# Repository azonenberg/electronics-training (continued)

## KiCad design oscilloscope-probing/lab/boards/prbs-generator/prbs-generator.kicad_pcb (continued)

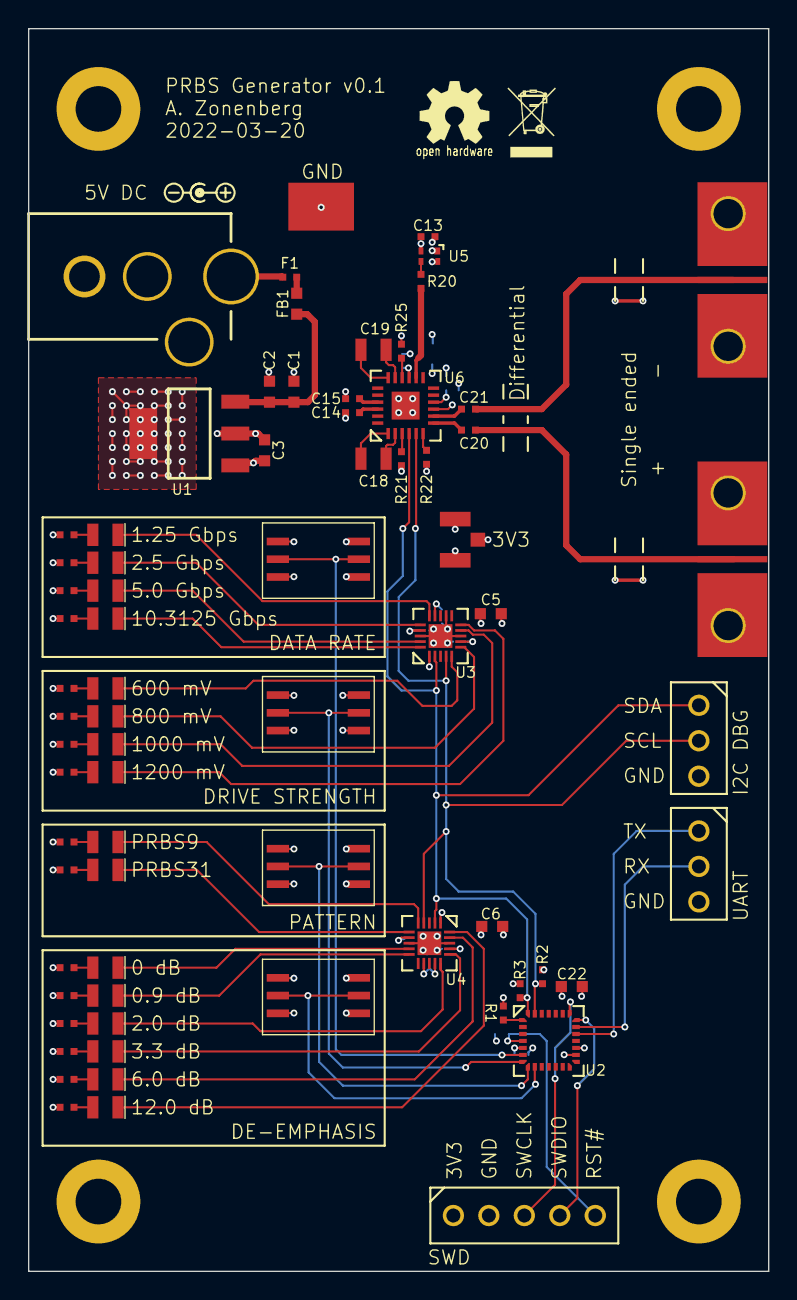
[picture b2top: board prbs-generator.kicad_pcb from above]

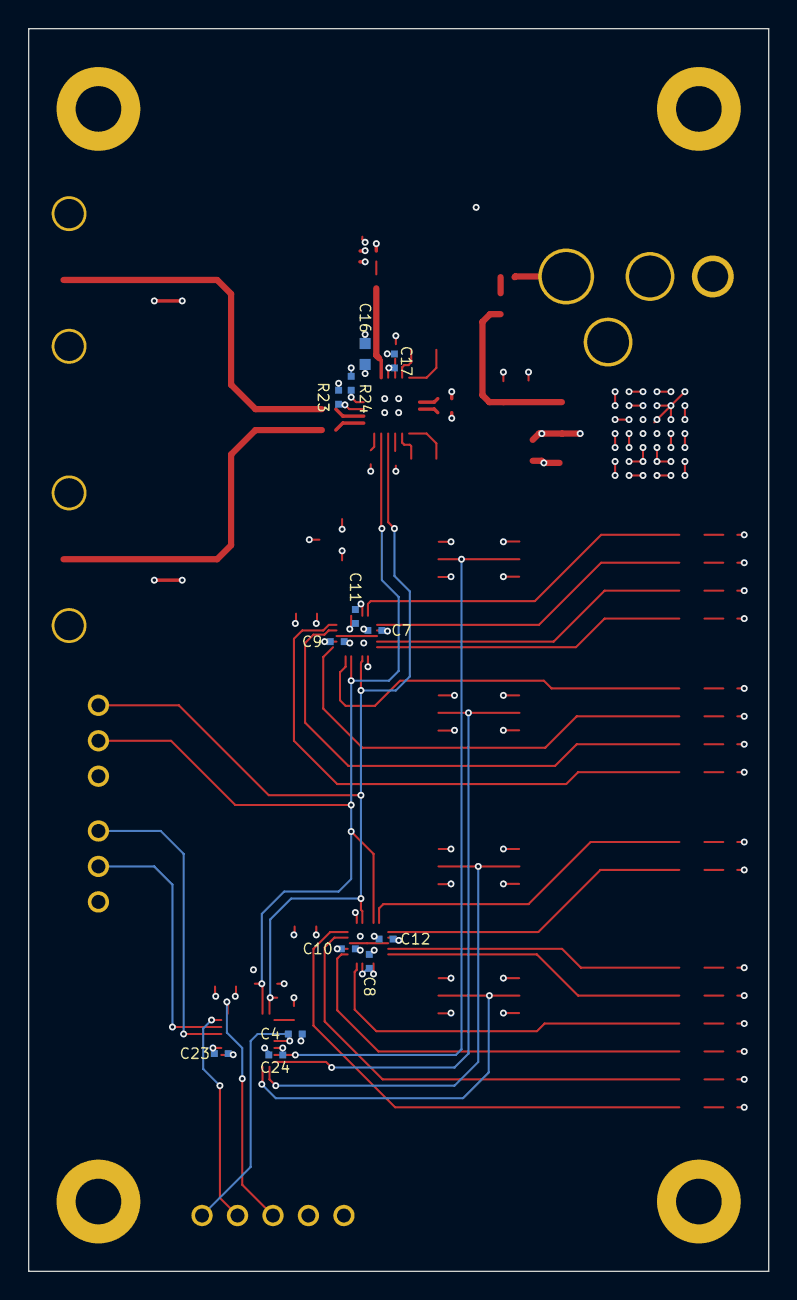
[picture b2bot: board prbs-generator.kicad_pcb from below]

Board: 4 copper layers, 53.0 x 89.0 mm, 92 parts (13 on the bottom side), 66 nets.

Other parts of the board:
G1: LOGO; Logo_silk_OSHW_6x6mm
G2: LOGO; Logo_silk_WEEE_3.4x5mm
G3: LOGO; Logo_silk_polarity_center_5x1.4mm

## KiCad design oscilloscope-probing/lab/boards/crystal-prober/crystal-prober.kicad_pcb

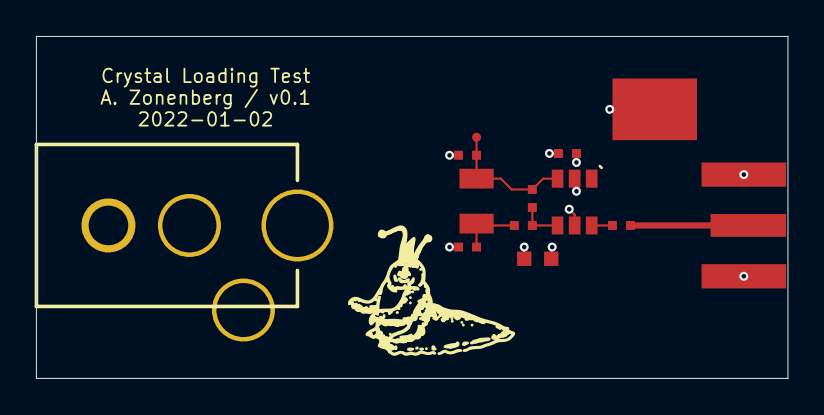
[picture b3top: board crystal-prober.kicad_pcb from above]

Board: 4 copper layers, 41.8 x 19.0 mm, 13 parts (0 on the bottom side), 7 nets.

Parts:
C1: 4.7 uF; EIA_0603_CAP_NOSILK
C2: 0.47 uF; EIA_0402_CAP_NOSILK
C3, C4: 8 pF; EIA_0402_CAP_NOSILK
J1: BARREL_JACK; CONN_CUI_PJ-058BH_HIPWR_BARREL_NOSLOT
J2: SMA-J-P-H-ST-EM1; CONN_SMA_EDGE_SAMTEC_SMA_J_P_H_ST_EM1
J3: TESTPOINT; TESTPOINT_SMT_0.5MM
J4: TESTCLIP; TESTPOINT_SMT_KEYSTONE_5016
R1: 1M; EIA_0402_RES_NOSILK
R2: 324K; EIA_0402_RES_NOSILK
R3: 33; EIA_0402_RES_NOSILK
U1: SN74LVC1GX04; SOT23_6
Y1: ABS07-32.768KHZ-4-T; CRYSTAL_3.2x1.5MM

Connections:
/3V3: C1.1, C2.1, J1.1, U1.5
/GND: C1.2, C2.2, C3.2, C4.2, J1.2, J2.2, J4.1, U1.2
/VOUT: R3.2, U1.6
/VOUT_TERM: J2.1, R3.1
/X1: C3.1, J3.1, R1.2, U1.3, Y1.1
/X2: R1.1, R2.1, U1.4
/X2X: C4.1, R2.2, Y1.2

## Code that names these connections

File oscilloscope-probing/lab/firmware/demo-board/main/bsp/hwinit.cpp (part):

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
void BSP_InitUART()
{
	//Initialize the UART for local console: 115.2 Kbps using PA9 for UART1 transmit and PA10 for UART1 receive
	//TODO: nice interface for enabling UART interrupts
	static GPIOPin uart_tx(&GPIOA, 9, GPIOPin::MODE_PERIPHERAL, GPIOPin::SLEW_SLOW, 7);
	static GPIOPin uart_rx(&GPIOA, 10, GPIOPin::MODE_PERIPHERAL, GPIOPin::SLEW_SLOW, 7);

	//Enable the UART interrupt
	NVIC_EnableIRQ(37);
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	//Wait a bit before initializing FMC in case something goes bad
	g_logTimer.Sleep(1000);

	static GPIOPin fmc_ad0(&GPIOD, 14, GPIOPin::MODE_PERIPHERAL, GPIOPin::SLEW_VERYFAST, 12);
	static GPIOPin fmc_ad1(&GPIOD, 15, GPIOPin::MODE_PERIPHERAL, GPIOPin::SLEW_VERYFAST, 12);
	static GPIOPin fmc_ad2(&GPIOD, 0, GPIOPin::MODE_PERIPHERAL, GPIOPin::SLEW_VERYFAST, 12);
	static GPIOPin fmc_ad3(&GPIOD, 1, GPIOPin::MODE_PERIPHERAL, GPIOPin::SLEW_VERYFAST, 12);
	static GPIOPin fmc_ad4(&GPIOE, 7, GPIOPin::MODE_PERIPHERAL, GPIOPin::SLEW_VERYFAST, 12);
	static GPIOPin fmc_ad5(&GPIOE, 8, GPIOPin::MODE_PERIPHERAL, GPIOPin::SLEW_VERYFAST, 12);
	static GPIOPin fmc_ad6(&GPIOE, 9, GPIOPin::MODE_PERIPHERAL, GPIOPin::SLEW_VERYFAST, 12);
	static GPIOPin fmc_ad7(&GPIOE, 10, GPIOPin::MODE_PERIPHERAL, GPIOPin::SLEW_VERYFAST, 12);
	static GPIOPin fmc_ad8(&GPIOE, 11, GPIOPin::MODE_PERIPHERAL, GPIOPin::SLEW_VERYFAST, 12);
	static GPIOPin fmc_ad9(&GPIOE, 12, GPIOPin::MODE_PERIPHERAL, GPIOPin::SLEW_VERYFAST, 12);
	static GPIOPin fmc_ad10(&GPIOE, 13, GPIOPin::MODE_PERIPHERAL, GPIOPin::SLEW_VERYFAST, 12);
	static GPIOPin fmc_ad11(&GPIOE, 14, GPIOPin::MODE_PERIPHERAL, GPIOPin::SLEW_VERYFAST, 12);
	static GPIOPin fmc_ad12(&GPIOE, 15, GPIOPin::MODE_PERIPHERAL, GPIOPin::SLEW_VERYFAST, 12);
	static GPIOPin fmc_ad13(&GPIOD, 8, GPIOPin::MODE_PERIPHERAL, GPIOPin::SLEW_VERYFAST, 12);
	static GPIOPin fmc_ad14(&GPIOD, 9, GPIOPin::MODE_PERIPHERAL, GPIOPin::SLEW_VERYFAST, 12);
	static GPIOPin fmc_ad15(&GPIOD, 10, GPIOPin::MODE_PERIPHERAL, GPIOPin::SLEW_VERYFAST, 12);

	static GPIOPin fmc_a16(&GPIOD, 11, GPIOPin::MODE_PERIPHERAL, GPIOPin::SLEW_VERYFAST, 12);
	static GPIOPin fmc_a17(&GPIOD, 12, GPIOPin::MODE_PERIPHERAL, GPIOPin::SLEW_VERYFAST, 12);
	static GPIOPin fmc_a18(&GPIOD, 13, GPIOPin::MODE_PERIPHERAL, GPIOPin::SLEW_VERYFAST, 12);
	static GPIOPin fmc_a19(&GPIOE, 3, GPIOPin::MODE_PERIPHERAL, GPIOPin::SLEW_VERYFAST, 12);
	static GPIOPin fmc_a20(&GPIOE, 4, GPIOPin::MODE_PERIPHERAL, GPIOPin::SLEW_VERYFAST, 12);
	static GPIOPin fmc_a21(&GPIOE, 5, GPIOPin::MODE_PERIPHERAL, GPIOPin::SLEW_VERYFAST, 12);
	static GPIOPin fmc_a22(&GPIOE, 6, GPIOPin::MODE_PERIPHERAL, GPIOPin::SLEW_VERYFAST, 12);
	//no A23...25 pinned out on this board

	static GPIOPin fmc_nl_nadv(&GPIOB, 7, GPIOPin::MODE_PERIPHERAL, GPIOPin::SLEW_VERYFAST, 12);
	static GPIOPin fmc_nwait(&GPIOD, 6, GPIOPin::MODE_PERIPHERAL, GPIOPin::SLEW_VERYFAST, 12);
	static GPIOPin fmc_ne1(&GPIOD, 7, GPIOPin::MODE_PERIPHERAL, GPIOPin::SLEW_VERYFAST, 12);
	static GPIOPin fmc_ne2(&GPIOC, 8, GPIOPin::MODE_PERIPHERAL, GPIOPin::SLEW_VERYFAST, 9);
	static GPIOPin fmc_ne3(&GPIOG, 6, GPIOPin::MODE_PERIPHERAL, GPIOPin::SLEW_VERYFAST, 12);
	static GPIOPin fmc_ne4(&GPIOG, 12, GPIOPin::MODE_PERIPHERAL, GPIOPin::SLEW_VERYFAST, 12);

	static GPIOPin fmc_clk(&GPIOD, 3, GPIOPin::MODE_PERIPHERAL, GPIOPin::SLEW_VERYFAST, 12);
	static GPIOPin fmc_noe(&GPIOD, 4, GPIOPin::MODE_PERIPHERAL, GPIOPin::SLEW_VERYFAST, 12);
	static GPIOPin fmc_nwe(&GPIOD, 5, GPIOPin::MODE_PERIPHERAL, GPIOPin::SLEW_VERYFAST, 12);
	static GPIOPin fmc_nbl0(&GPIOE, 0, GPIOPin::MODE_PERIPHERAL, GPIOPin::SLEW_VERYFAST, 12);
	static GPIOPin fmc_nbl1(&GPIOE, 1, GPIOPin::MODE_PERIPHERAL, GPIOPin::SLEW_VERYFAST, 12);

	//Add a pullup on NWAIT
	fmc_nwait.SetPullMode(GPIOPin::PULL_UP);

	InitFMCForFPGA();

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
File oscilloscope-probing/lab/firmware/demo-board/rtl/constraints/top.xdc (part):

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set_property PACKAGE_PIN C14 [get_ports {pmod_io[1]}]
set_property PACKAGE_PIN B13 [get_ports {pmod_io[0]}]
set_property IOSTANDARD LVCMOS33 [get_ports clk_25mhz]
set_property PACKAGE_PIN W19 [get_ports clk_25mhz]
set_property PACKAGE_PIN T19 [get_ports flash_cs_n]
set_property IOSTANDARD LVCMOS33 [get_ports flash_cs_n]
set_property PACKAGE_PIN Y18 [get_ports fmc_clk]
set_property IOSTANDARD LVCMOS33 [get_ports fmc_clk]
set_property PACKAGE_PIN P16 [get_ports fmc_ne1]
set_property IOSTANDARD LVCMOS33 [get_ports fmc_ne1]
set_property PACKAGE_PIN T21 [get_ports fmc_ne2]
set_property IOSTANDARD LVCMOS33 [get_ports fmc_ne2]
set_property PACKAGE_PIN T18 [get_ports fmc_ne3]
set_property IOSTANDARD LVCMOS33 [get_ports fmc_ne3]
set_property PACKAGE_PIN R14 [get_ports fmc_ne4]
set_property IOSTANDARD LVCMOS33 [get_ports fmc_ne4]
set_property PACKAGE_PIN V20 [get_ports fmc_nl_nadv]
set_property IOSTANDARD LVCMOS33 [get_ports fmc_nl_nadv]
set_property PACKAGE_PIN U17 [get_ports fmc_noe]
set_property IOSTANDARD LVCMOS33 [get_ports fmc_noe]
set_property PACKAGE_PIN V17 [get_ports fmc_nwait]
set_property IOSTANDARD LVCMOS33 [get_ports fmc_nwait]
set_property PACKAGE_PIN R16 [get_ports fmc_nwe]
set_property IOSTANDARD LVCMOS33 [get_ports fmc_nwe]
set_property PACKAGE_PIN B21 [get_ports led_ctrl]
set_property IOSTANDARD LVCMOS33 [get_ports led_ctrl]
set_property DRIVE 4 [get_ports led_ctrl]
set_property SLEW SLOW [get_ports led_ctrl]
set_property PACKAGE_PIN R19 [get_ports pam3_tx_n]
set_property IOSTANDARD LVCMOS33 [get_ports pam3_tx_n]
set_property SLEW SLOW [get_ports pam3_tx_n]
set_property PACKAGE_PIN P19 [get_ports pam3_tx_p]
set_property IOSTANDARD LVCMOS33 [get_ports pam3_tx_p]
set_property SLEW SLOW [get_ports pam3_tx_p]
set_property PACKAGE_PIN A18 [get_ports uart_cts_n]
set_property PACKAGE_PIN A16 [get_ports {pmod_io[7]}]
set_property PACKAGE_PIN A21 [get_ports uart_rts_n]
set_property IOSTANDARD LVCMOS33 [get_ports uart_cts_n]
set_property IOSTANDARD LVCMOS33 [get_ports uart_rts_n]
set_property PACKAGE_PIN A20 [get_ports uart_rx]
set_property PACKAGE_PIN A19 [get_ports uart_tx]
set_property IOSTANDARD LVCMOS33 [get_ports uart_rx]
set_property IOSTANDARD LVCMOS33 [get_ports uart_tx]
set_property DRIVE 4 [get_ports uart_tx]
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set_property DRIVE 4 [get_ports uart_rts_n]
set_property SLEW SLOW [get_ports uart_rts_n]

set_property PACKAGE_PIN F6 [get_ports gtp_ref_p]

set_property PULLTYPE PULLUP [get_ports fmc_ne1]
set_property PULLTYPE PULLUP [get_ports fmc_ne2]
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set_property DRIVE 16 [get_ports {coax_out[0]}]


set_property PACKAGE_PIN B4 [get_ports gtp_tx0_p]
set_property PACKAGE_PIN D5 [get_ports gtp_tx1_p]

create_clock -period 6.400 -name gtp_ref_p -waveform {0.000 3.200} [get_ports gtp_ref_p]

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
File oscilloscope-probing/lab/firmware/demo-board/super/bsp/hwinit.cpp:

/***********************************************************************************************************************
*                                                                                                                      *
* electronics-training                                                                                                 *
*                                                                                                                      *
* Copyright (c) 2023-2026 Andrew D. Zonenberg and contributors                                                         *
* All rights reserved.                                                                                                 *
*                                                                                                                      *
* Redistribution and use in source and binary forms, with or without modification, are permitted provided that the     *
* following conditions are met:                                                                                        *
*                                                                                                                      *
*    * Redistributions of source code must retain the above copyright notice, this list of conditions, and the         *
*      following disclaimer.                                                                                           *
*                                                                                                                      *
*    * Redistributions in binary form must reproduce the above copyright notice, this list of conditions and the       *
*      following disclaimer in the documentation and/or other materials provided with the distribution.                *
*                                                                                                                      *
*    * Neither the name of the author nor the names of any contributors may be used to endorse or promote products     *
*      derived from this software without specific prior written permission.                                           *
*                                                                                                                      *
* THIS SOFTWARE IS PROVIDED BY THE AUTHORS "AS IS" AND ANY EXPRESS OR IMPLIED WARRANTIES, INCLUDING, BUT NOT LIMITED   *
* TO, THE IMPLIED WARRANTIES OF MERCHANTABILITY AND FITNESS FOR A PARTICULAR PURPOSE ARE DISCLAIMED. IN NO EVENT SHALL *
* THE AUTHORS BE HELD LIABLE FOR ANY DIRECT, INDIRECT, INCIDENTAL, SPECIAL, EXEMPLARY, OR CONSEQUENTIAL DAMAGES        *
* (INCLUDING, BUT NOT LIMITED TO, PROCUREMENT OF SUBSTITUTE GOODS OR SERVICES; LOSS OF USE, DATA, OR PROFITS; OR       *
* BUSINESS INTERRUPTION) HOWEVER CAUSED AND ON ANY THEORY OF LIABILITY, WHETHER IN CONTRACT, STRICT LIABILITY, OR TORT *
* (INCLUDING NEGLIGENCE OR OTHERWISE) ARISING IN ANY WAY OUT OF THE USE OF THIS SOFTWARE, EVEN IF ADVISED OF THE       *
* POSSIBILITY OF SUCH DAMAGE.                                                                                          *
*                                                                                                                      *
***********************************************************************************************************************/

/**
	@file
	@author	Andrew D. Zonenberg
	@brief	Boot-time hardware initialization
 */
#include <core/platform.h>
#include <supervisor/supervisor-common.h>
#include "hwinit.h"
#include <peripheral/Power.h>

////////////////////////////////////////////////////////////////////////////////////////////////////////////////////////
// System status indicator LEDs

GPIOPin g_pgoodLED(&GPIOB, 13, GPIOPin::MODE_OUTPUT, GPIOPin::SLEW_SLOW);
GPIOPin g_faultLED(&GPIOB, 15, GPIOPin::MODE_OUTPUT, GPIOPin::SLEW_SLOW);
GPIOPin g_sysokLED(&GPIOB, 14, GPIOPin::MODE_OUTPUT, GPIOPin::SLEW_SLOW);

////////////////////////////////////////////////////////////////////////////////////////////////////////////////////////
// Common global hardware config used by both bootloader and application

//UART console
//USART1 is on APB1 (80 MHz), so we need a divisor of 694.44, round to 694
UART<16, 256> g_uart(&USART1, 694);

//I2C1 defaults to running of APB clock (80 MHz)
//Prescale by 4 to get 20 MHz
//Divide by 50 after that to get 400 kHz
I2C g_i2c(&I2C1, 4, 50);

////////////////////////////////////////////////////////////////////////////////////////////////////////////////////////
// Low level init

void BSP_InitUART()
{
	//Initialize the UART for local console: 115.2 Kbps
	//TODO: nice interface for enabling UART interrupts
	GPIOPin uart_tx(&GPIOA, 9, GPIOPin::MODE_PERIPHERAL, GPIOPin::SLEW_SLOW, 7);
	GPIOPin uart_rx(&GPIOA, 10, GPIOPin::MODE_PERIPHERAL, GPIOPin::SLEW_SLOW, 7);

	g_logTimer.Sleep(10);	//wait for UART pins to be high long enough to remove any glitches during powerup

	//Enable the UART interrupt
	NVIC_EnableIRQ(37);
}

////////////////////////////////////////////////////////////////////////////////////////////////////////////////////////
// Common features shared by both application and bootloader

void BSP_Init()
{
	InitGPIOs();
	Super_Init();

	App_Init();
}

////////////////////////////////////////////////////////////////////////////////////////////////////////////////////////
// GPIOs for all of the rail enables

void InitGPIOs()
{
	g_log("Initializing GPIOs\n");

	//turn off all LEDs
	g_pgoodLED = 0;
	g_faultLED = 0;
	g_sysokLED = 0;

	//Set up GPIOs for I2C bus
	static GPIOPin i2c_scl(&GPIOB, 6, GPIOPin::MODE_PERIPHERAL, GPIOPin::SLEW_SLOW, 4, true);
	static GPIOPin i2c_sda(&GPIOB, 7, GPIOPin::MODE_PERIPHERAL, GPIOPin::SLEW_SLOW, 4, true);
}

float GetLTCTemp()
{
	//220 mV at 25C plus 7 mV/c
	float vtemp = g_adc->ReadChannelScaledAveraged(5, 4, 3.3);
	return ((vtemp - 0.22) / 0.007) + 25;
}

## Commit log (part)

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2021-11-28 Initial import of probing talk and some support files. Changed license from BSD-3 to CC BY-SA 4.0
2021-12-20 Added lots more figures
2021-12-20 Added README and initial lab outline notes
2021-12-20 Updated probing lecture slides with lots of new content
2021-12-22 Added lots of new sections, data on BNC terminations and power rail probes
2021-12-25 Lots more material on cheap probe, new scopevna resuilts, new sections on HV and current probing
2021-12-25 Lots of new content around probe loading and differential probes
2021-12-26 Added more figures
2021-12-27 Slide version used in today's test lecture
2022-01-03 Initial version of crystal-prober
2022-03-20 Initial work on PRBS generator
2022-03-20 Continued work on PRBS board layout
2022-03-20 Finished initial PRBS generator
2022-04-01 Added firmware submodules
2022-04-01 Initial UI side of firmware (LEDs/buttons) is done. Doesn't configure the retimer yet, but does everything else
2022-04-01 Finished initial firmware for PRBS generator
2022-04-01 Fixed bug where emphasis of 12 cycled to 0.9 not 0.0
2022-04-02 Bug fix: added 250ms delay to ensure I2C devices are ready to accept commands before starting to configure them
2022-05-10 Updated lecture notes, added a lot more media files
2023-11-12 Began work on new sectional slide deck, haven't migrated everything over yet
2023-11-12 Finished refactoring of probing class into separate slide decks per section
2023-11-16 Continued revamping slides, major work on sections 3/4
2023-11-16 Started adding TDR response data
